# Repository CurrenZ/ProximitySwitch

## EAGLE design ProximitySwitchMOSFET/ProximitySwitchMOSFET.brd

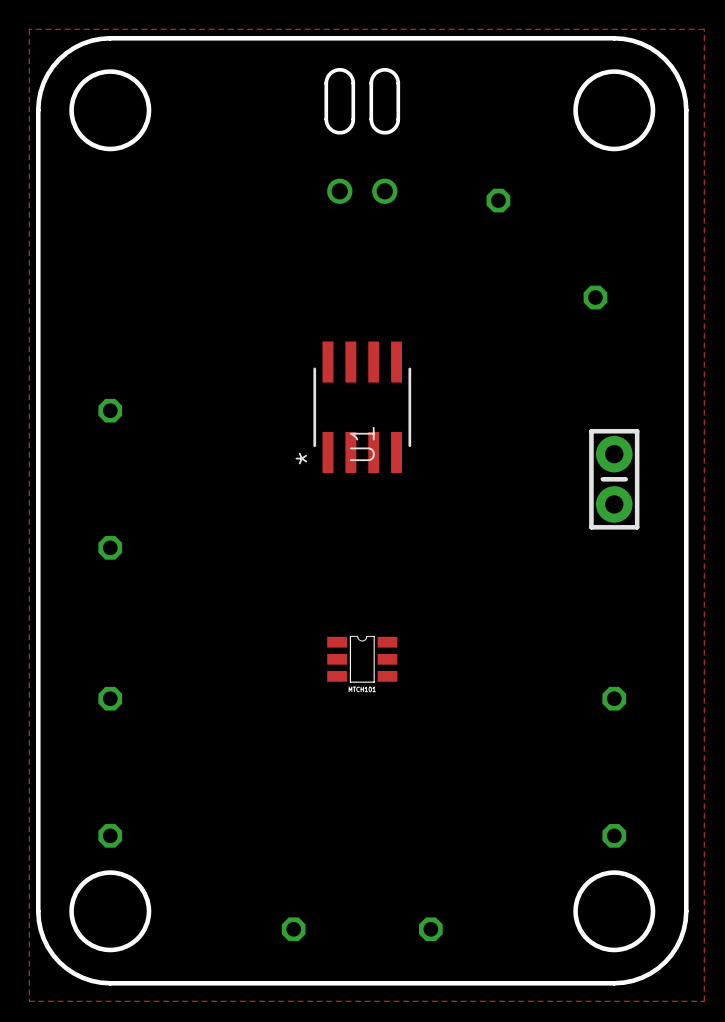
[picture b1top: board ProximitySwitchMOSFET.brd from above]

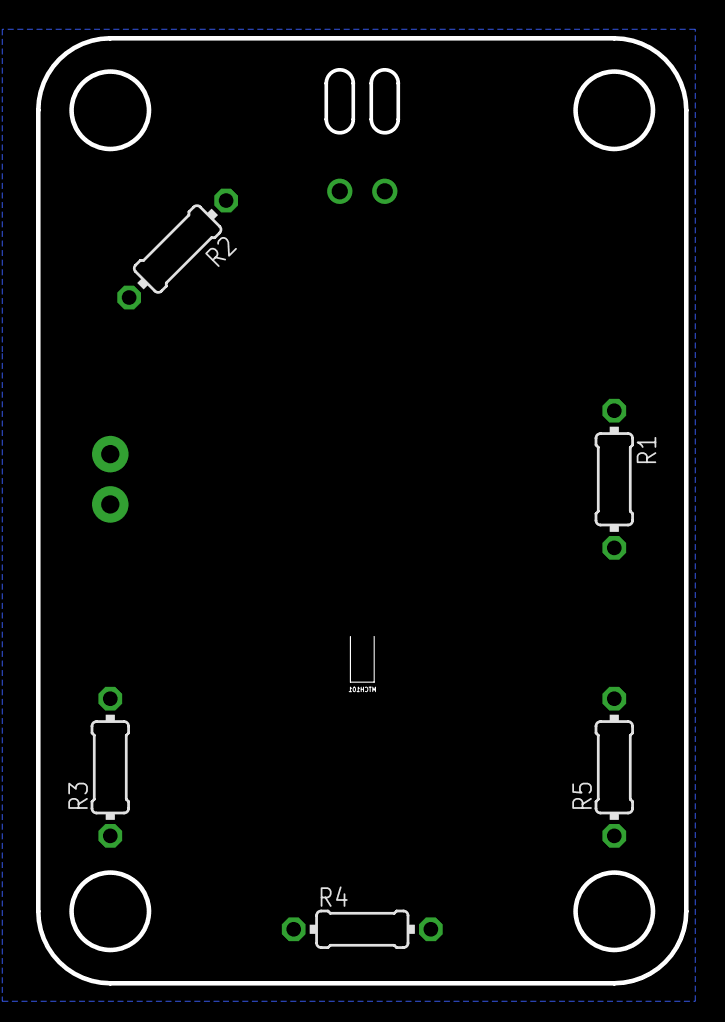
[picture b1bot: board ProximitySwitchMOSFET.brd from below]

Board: 2 copper layers, 36.0 x 52.5 mm, 9 parts (5 on the bottom side), 9 nets, no tracks yet.

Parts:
C1: 0.1uF; CAP-PTH-SMALL-KIT
R1, R2, R3, R4, R5: RESISTOR_0204/7
U1: 4936BM08A-M; M08A-M
U$1: MTCH101
U$2: MONO_WIRE

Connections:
GND: C1.2, R4.1, U$1.VSS
unnamed: R5.2, U$1.MTSA
unnamed: R3.1, R4.2, R5.1
unnamed: R1.2, U$1.MTI
unnamed: R2.1, U$1.MTPM
unnamed: U1.1, U1.3, U$1.MTO
unnamed: U1.5, U$2.P$2
unnamed: C1.1, R2.2, R3.2, U1.2, U1.4, U$1.VDD
unnamed: U1.8, U$2.P$1
